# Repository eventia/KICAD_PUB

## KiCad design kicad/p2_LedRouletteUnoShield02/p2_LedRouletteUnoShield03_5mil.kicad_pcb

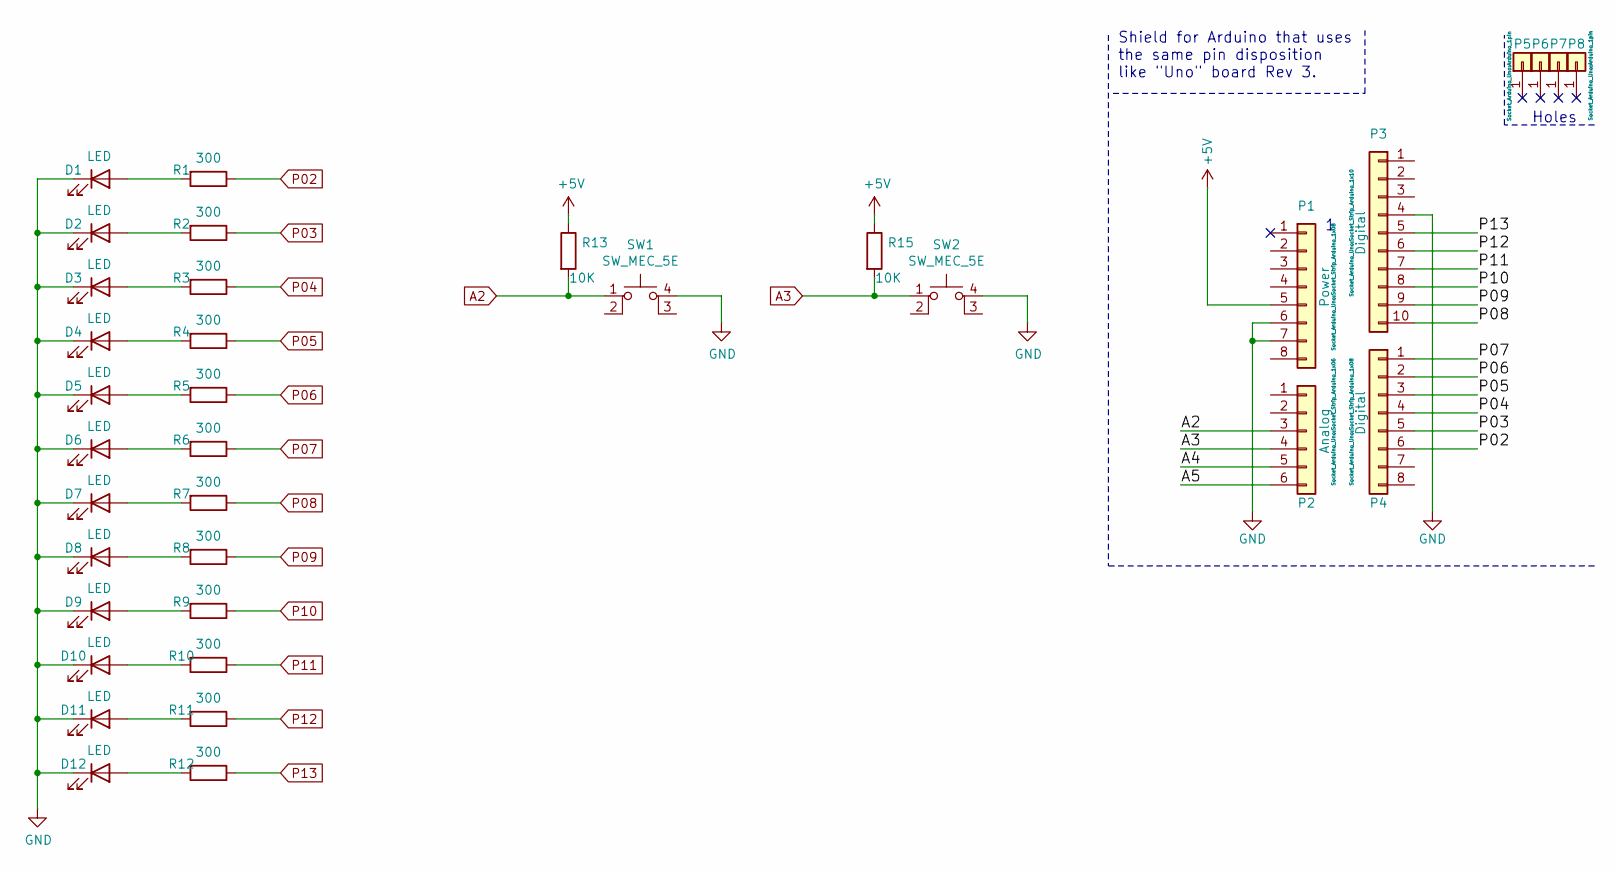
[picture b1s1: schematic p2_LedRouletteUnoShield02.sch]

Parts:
D1, D2, D3, D4, D5, D6, D7, D8, D9, D10, D11, D12: LED; LED_D5.0mm
P1: Power; Socket_Strip_Arduino_1x08
P2: Analog; Socket_Strip_Arduino_1x06
P3: Digital; Socket_Strip_Arduino_1x10
P4: Digital; Socket_Strip_Arduino_1x08
P5, P6, P7, P8: CONN_01X01; Arduino_1pin
R1, R2, R3, R4, R5, R6, R7, R8, R9, R10, R11, R12: 300; R_Axial_DIN0207_L6.3mm_D2.5mm_P7.62mm_Horizontal
R13, R15: 10K; R_Axial_DIN0207_L6.3mm_D2.5mm_P7.62mm_Horizontal
SW1, SW2: SW_MEC_5E; SW_TH_Tactile_Omron_B3F-10xx

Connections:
+5V: P1.5, R13.1, R15.1
/A4: P3.2
/A5: P3.1
A2: P2.3, R13.2, SW1.1
A3: P2.4, R15.2, SW2.1
GND: D1.1 (K), D2.1 (K), D3.1 (K), D4.1 (K), D5.1 (K), D6.1 (K), D7.1 (K), D8.1 (K), D9.1 (K), D10.1 (K), D11.1 (K), D12.1 (K), P1.6, P1.7, P3.4, SW1.4 (A), SW2.4 (A)
unnamed: D1.2 (A), R1.2
unnamed: D2.2 (A), R2.2
unnamed: D3.2 (A), R3.2
unnamed: D4.2 (A), R4.2
unnamed: D5.2 (A), R5.2
unnamed: D6.2 (A), R6.2
unnamed: D7.2 (A), R7.2
unnamed: D8.2 (A), R8.2
unnamed: D9.2 (A), R9.2
unnamed: D10.2 (A), R10.2
unnamed: D11.2 (A), R11.2
unnamed: D12.2 (A), R12.2
P02: P4.6, R1.1
P03: P4.5, R2.1
P04: P4.4, R3.1
P05: P4.3, R4.1
P06: P4.2, R5.1
P07: P4.1, R6.1
P08: P3.10, R7.1
P09: P3.9, R8.1
P10: P3.8, R9.1
P11: P3.7, R10.1
P12: P3.6, R11.1
P13: P3.5, R12.1

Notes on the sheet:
Holes
Shield for Arduino that uses the same pin disposition like "Uno" board Rev 3.

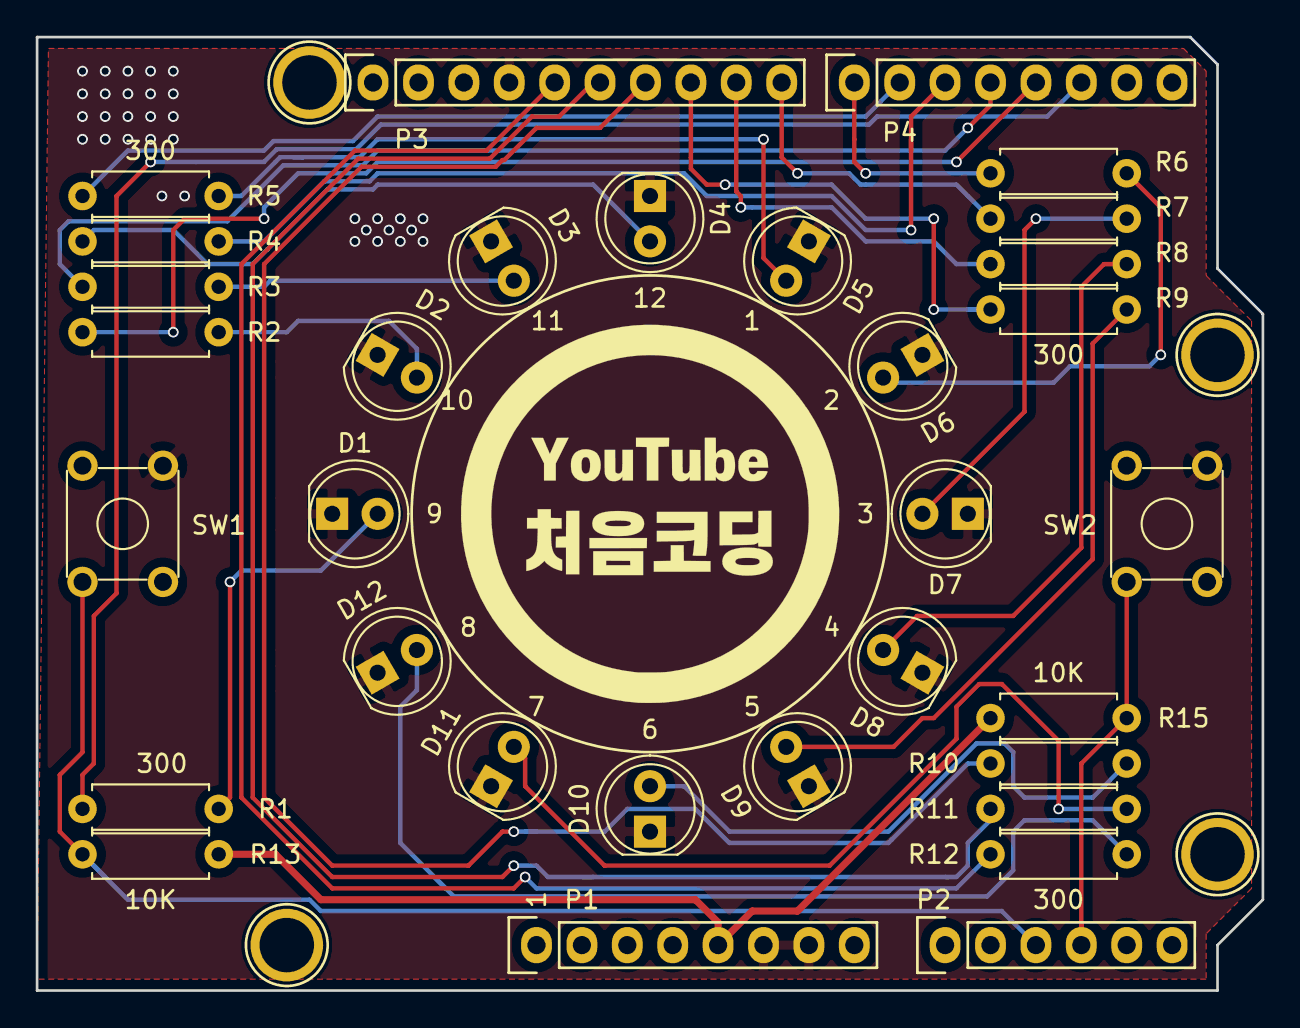
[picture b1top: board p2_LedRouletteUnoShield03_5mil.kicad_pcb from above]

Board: 2 copper layers, 68.6 x 53.3 mm, 36 parts (0 on the bottom side), 28 nets.
